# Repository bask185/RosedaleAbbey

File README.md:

# all source code used for rosedale abbey

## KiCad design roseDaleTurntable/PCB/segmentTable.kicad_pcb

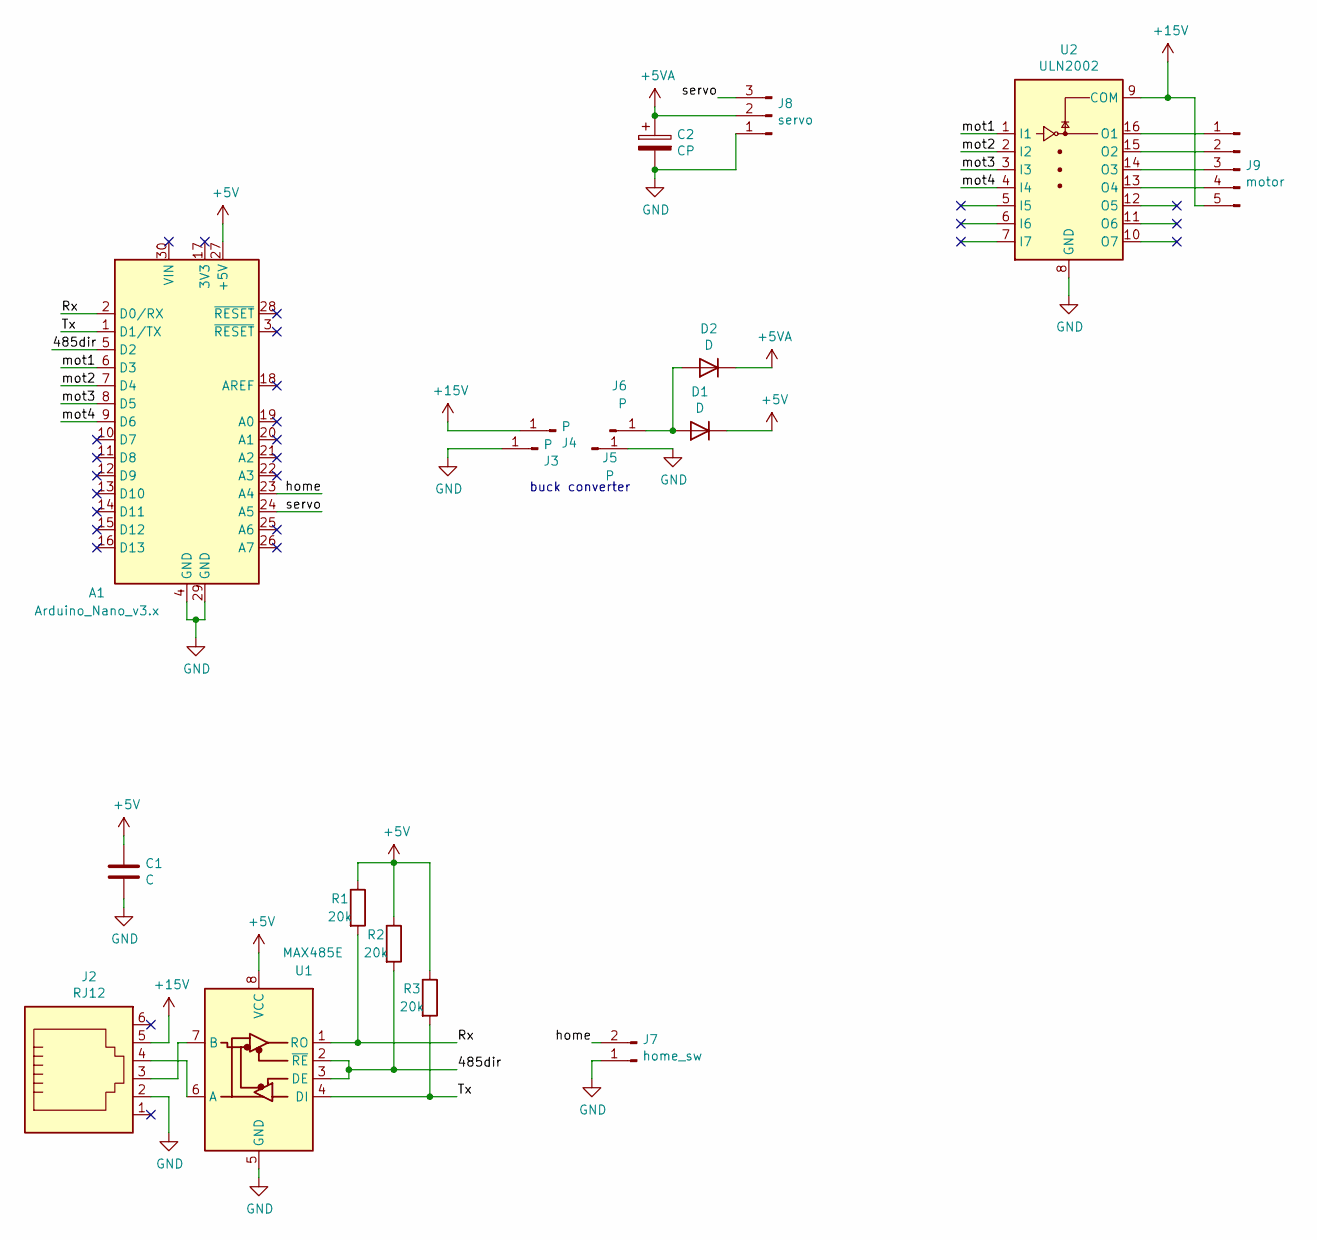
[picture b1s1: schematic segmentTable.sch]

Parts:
A1: Arduino_Nano_v3.x; Arduino_Nano
C1: C; C_Disc_D3.0mm_W1.6mm_P2.50mm
C2: CP; CP_Radial_D4.0mm_P1.50mm
D1, D2: D; D_DO-34_SOD68_P7.62mm_Horizontal
J2: RJ12; RJ25_Wayconn_MJEA-660X1_Horizontal
J3, J4, J5, J6: P; TestPoint_Pad_3.0x3.0mm
J7: home_sw; PinSocket_1x02_P2.54mm_Vertical
J8: servo; PinHeader_1x03_P2.54mm_Vertical
J9: motor; JST_XH_B5B-XH-A_1x05_P2.50mm_Vertical
R1, R2, R3: 20k; R_Axial_DIN0204_L3.6mm_D1.6mm_P7.62mm_Horizontal
U1: MAX485E; DIP-8_W7.62mm
U2: ULN2002; DIP-16_W7.62mm

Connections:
+5V: A1.27 (+5V), C1.1, D1.1 (K), R1.1, R2.1, R3.1, U1.8 (VCC)
+5VA: C2.1, D2.1 (K), J8.2
+15V: J2.5, J4.1, J9.5, U2.9 (COM)
/485dir: A1.5 (D2), R2.2, U1.2 (~RE), U1.3 (DE)
/Rx: A1.2 (D0/RX), R1.2, U1.1 (RO)
/Tx: A1.1 (D1/TX), R3.2, U1.4 (DI)
/home: A1.23 (A4), J7.2
/mot1: A1.6 (D3), U2.1 (I1)
/mot2: A1.7 (D4), U2.2 (I2)
/mot3: A1.8 (D5), U2.3 (I3)
/mot4: A1.9 (D6), U2.4 (I4)
/servo: A1.24 (A5), J8.3
GND: A1.4 (GND), A1.29 (GND), C1.2, C2.2, J2.2, J3.1, J5.1, J7.1, J8.1, U1.5 (GND), U2.8 (GND)
unnamed: D1.2 (A), D2.2 (A), J6.1
unnamed: J2.3, U1.7 (B)
unnamed: J2.4, U1.6 (A)
unnamed: J9.1, U2.16 (O1)
unnamed: J9.2, U2.15 (O2)
unnamed: J9.3, U2.14 (O3)
unnamed: J9.4, U2.13 (O4)

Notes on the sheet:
buck converter

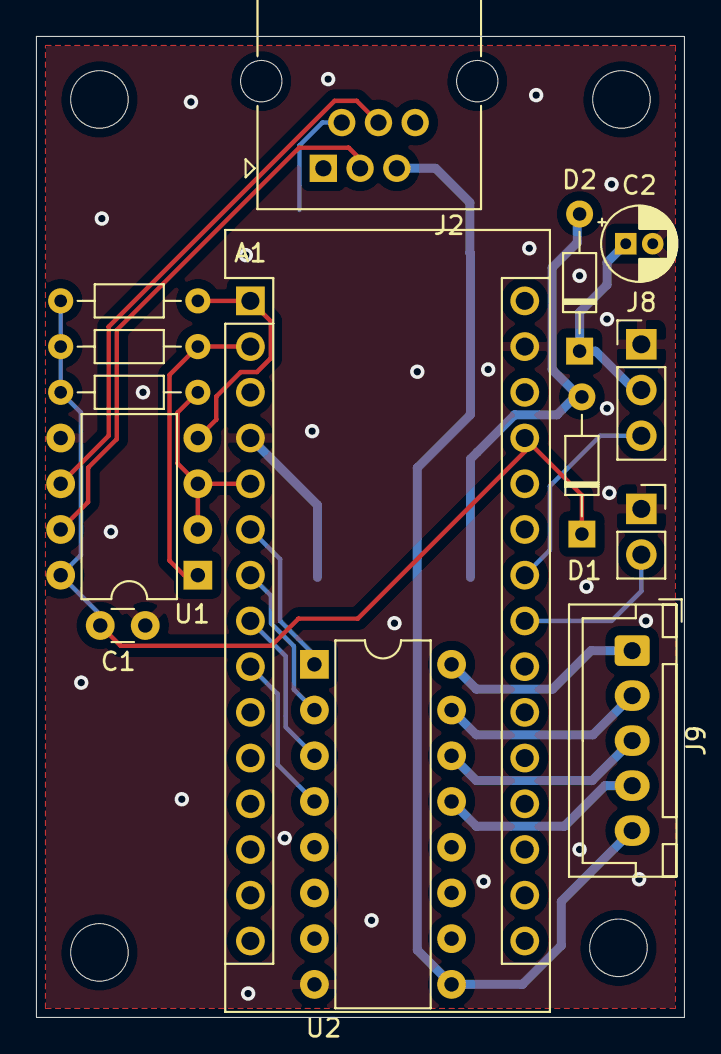
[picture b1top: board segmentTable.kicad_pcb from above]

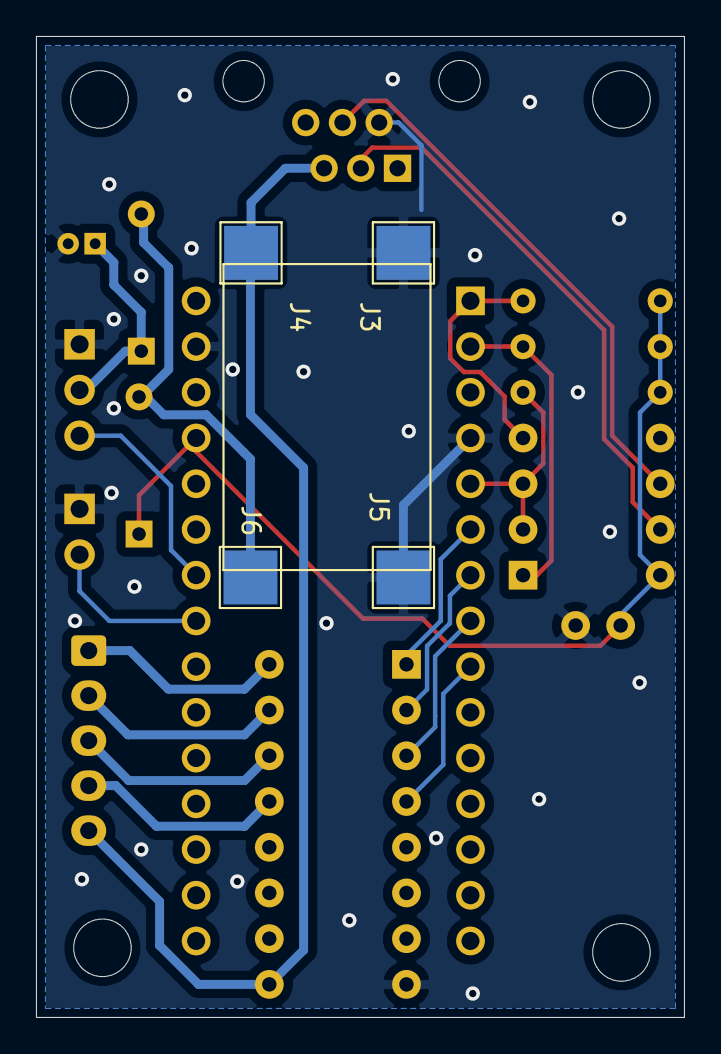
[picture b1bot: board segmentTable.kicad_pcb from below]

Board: 2 copper layers, 36.0 x 54.5 mm, 18 parts (4 on the bottom side), 20 nets.

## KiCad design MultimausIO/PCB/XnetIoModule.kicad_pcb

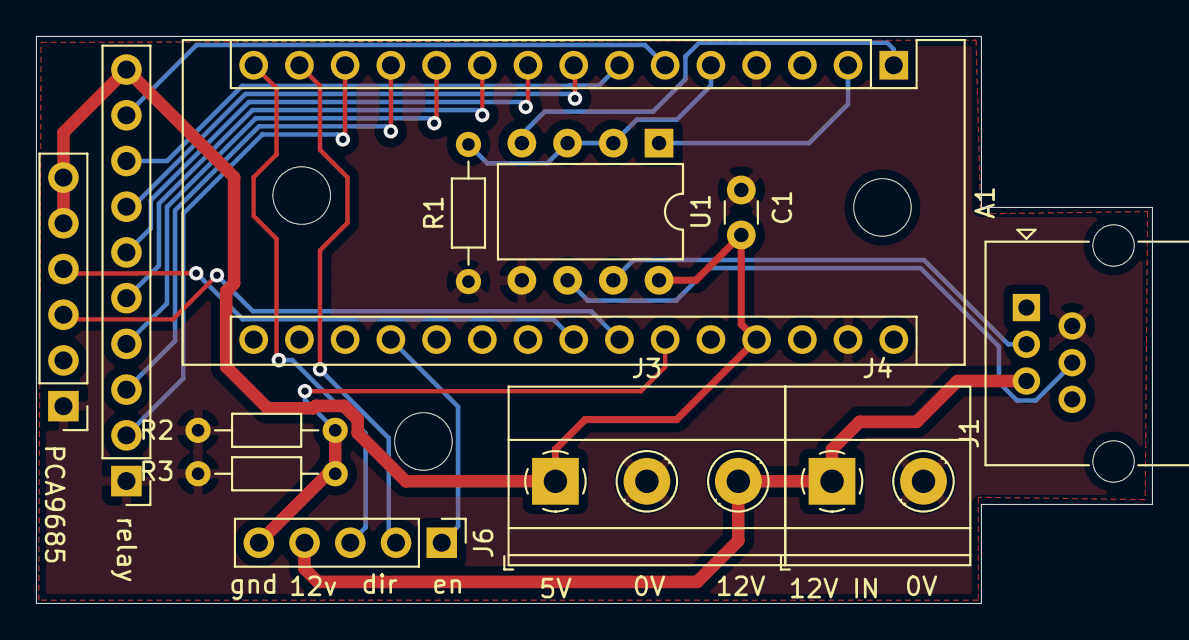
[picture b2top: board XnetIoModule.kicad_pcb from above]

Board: 2 copper layers, 62.0 x 31.5 mm, 12 parts (0 on the bottom side), 22 nets.

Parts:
A1: Arduino_Nano_v3.x; Arduino_Nano
C1: C; C_Disc_D3.0mm_W1.6mm_P2.50mm
J1: 6P6C; RJ25_Wayconn_MJEA-660X1_Horizontal
J3: DC-DC; TerminalBlock_Phoenix_MKDS-1,5-3-5.08_1x03_P5.08mm_Horizont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
J4: power_in; TerminalBlock_Phoenix_MKDS-1,5-2-5.08_1x02_P5.08mm_Horizont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
J6: PWM; PinHeader_1x05_P2.54mm_Vertical
PCA9685: PCA9685; PinHeader_1x06_P2.54mm_Vertical
R1: R; R_Axial_DIN0204_L3.6mm_D1.6mm_P7.62mm_Horizontal
R2, R3: 1R; R_Axial_DIN0204_L3.6mm_D1.6mm_P7.62mm_Horizontal
U1: MAX485E; DIP-8_W7.62mm
relay: relay; PinHeader_1x10_P2.54mm_Vertical

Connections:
+5V: A1.27, C1.1, J3.1, PCA9685.5, PCA9685.6, U1.8, relay.10
+12V: J1.5, J3.3, J4.1, J6.4
/CS: A1.25, J6.5, R2.1, R3.1
/En: A1.19, J6.1
/Rel1: A1.6, relay.9
/Rel2: A1.7, relay.8
/Rel3: A1.8, relay.7
/Rel4: A1.9, relay.6
/Rel5: A1.10, relay.5
/Rel6: A1.11, relay.4
/Rel7: A1.12, relay.3
/Rel8: A1.13, relay.2
/Rx: A1.2, U1.1
/SCL: A1.24, PCA9685.3
/SDA: A1.23, PCA9685.4
/Tx: A1.1, U1.4
/dir: A1.5, R1.2, U1.2, U1.3
/dir1: A1.14, J6.2
/dir2: A1.15, J6.3
GND: A1.4, A1.29, C1.2, J1.2, J3.2, J4.2, PCA9685.1, R1.1, R2.2, R3.2, U1.5, relay.1
unnamed: J1.3, U1.7
unnamed: J1.4, U1.6

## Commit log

2022-04-20 changed folder structure and added the event code from multimaus enhancer. I also heavily changed the code to make it more multipurpose.
    I am going to add serial functions to interract with this new code so I can test on the dry with the serial monitor
2022-04-24 succesfully implemented the recording/playing feature of the multimaus enhancer
2022-06-07 changed the recording start address to beyond the point positions. This should no longer overwrite servo positions
2022-06-07 some minor tweaking. May have fixed the routes...
    I do want to couple some relays to points to create 'self thinking points'
